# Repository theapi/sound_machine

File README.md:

# sound_machine
Use motion to select sounds

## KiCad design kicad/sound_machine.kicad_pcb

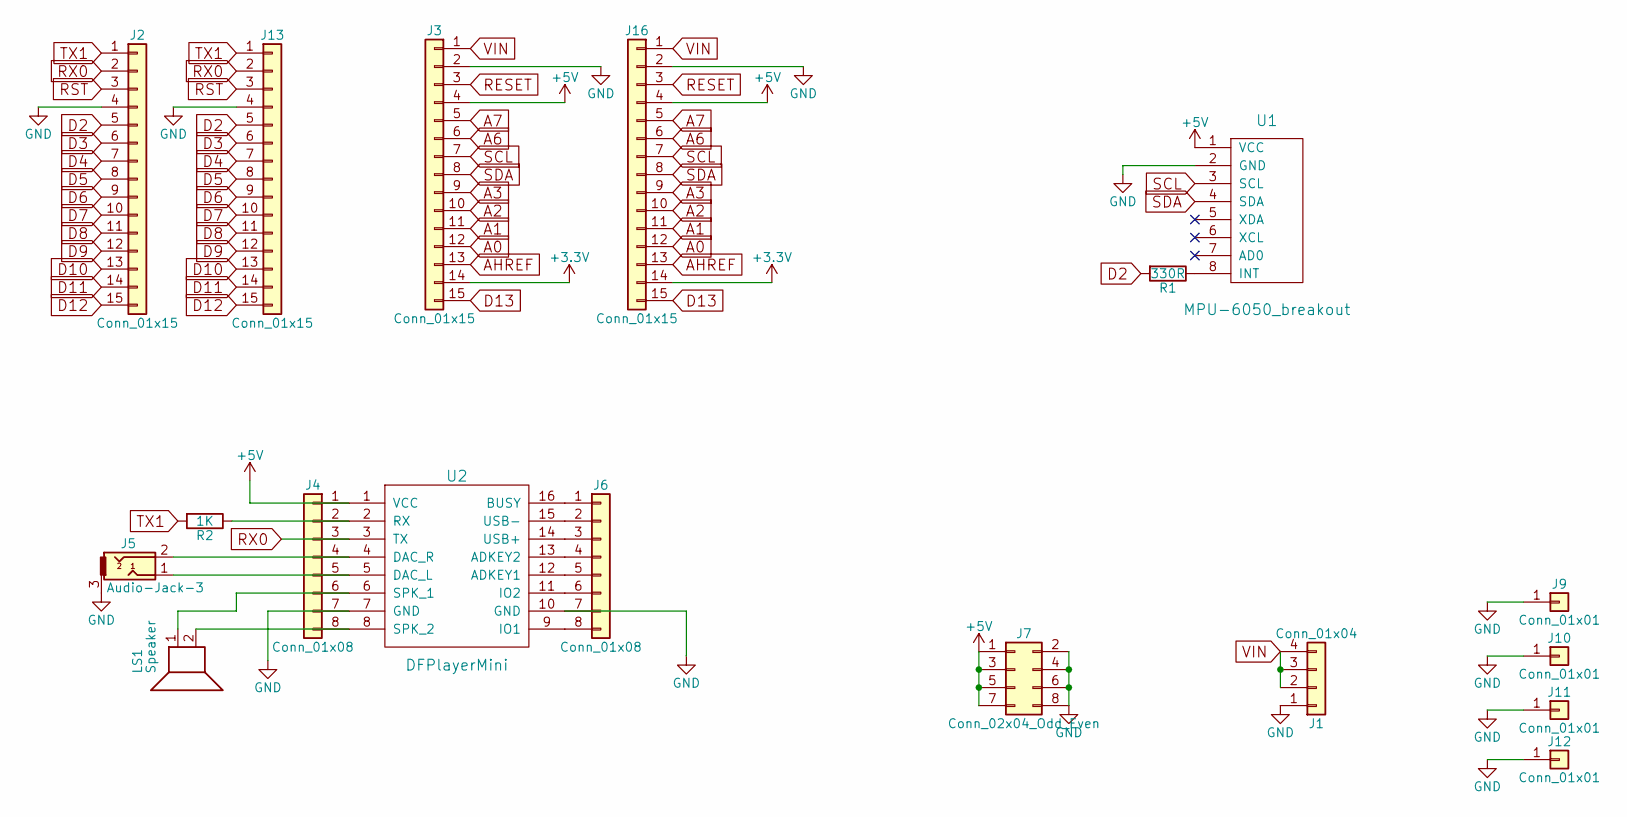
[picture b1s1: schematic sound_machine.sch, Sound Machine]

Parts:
J1: Conn_01x04; Pin_Header_Straight_1x04_Pitch2.54mm
J2, J3, J13, J16: Conn_01x15; Pin_Header_Straight_1x15_Pitch2.54mm
J4, J6: Conn_01x08; Pin_Header_Straight_1x08_Pitch2.54mm
J5: Audio-Jack-3; BARREL_JACK
J7: Conn_02x04_Odd_Even; Pin_Header_Straight_2x04_Pitch2.54mm
J9, J10, J11, J12: Conn_01x01; MountingHole_3.2mm_M3_DIN965_Pad
LS1: Speaker; Pin_Header_Straight_1x02_Pitch2.54mm
R1: 330R; R_0805_HandSoldering
R2: 1K; R_0805_HandSoldering
U1: MPU-6050_breakout; MPU-6050
U2: DFPlayerMini

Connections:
+3V3: J3.14, J16.14
+5V: J3.4, J4.1, J7.1, J7.3, J7.5, J7.7, J16.4, U1.1 (VCC), U2.1 (VCC)
A0: J3.12, J16.12
A1: J3.11, J16.11
A2: J3.10, J16.10
A3: J3.9, J16.9
A6: J3.6, J16.6
A7: J3.5, J16.5
AHREF: J3.13, J16.13
D2: J2.5, J13.5, R1.2
D3: J2.6, J13.6
D4: J2.7, J13.7
D5: J2.8, J13.8
D6: J2.9, J13.9
D7: J2.10, J13.10
D8: J2.11, J13.11
D9: J2.12, J13.12
D10: J2.13, J13.13
D11: J2.14, J13.14
D12: J2.15, J13.15
D13: J3.15, J16.15
GND: J1.1, J2.4, J3.2, J4.7, J5.3, J6.7, J7.2, J7.4, J7.6, J7.8, J9.1, J10.1, J11.1, J12.1, J13.4, J16.2, U1.2 (GND), U2.7 (GND), U2.10 (GND)
unnamed: J4.2, R2.1, U2.2 (RX)
unnamed: J4.4, J5.2, U2.4 (DAC_R)
unnamed: J4.5, J5.1, U2.5 (DAC_L)
unnamed: J4.6, LS1.1, U2.6 (SPK_1)
unnamed: J4.8, LS1.2, U2.8 (SPK_2)
unnamed: J6.1, U2.16 (BUSY)
unnamed: J6.2, U2.15 (USB-)
unnamed: J6.3, U2.14 (USB+)
unnamed: J6.4, U2.13 (ADKEY2)
unnamed: J6.5, U2.12 (ADKEY1)
unnamed: J6.6, U2.11 (IO2)
unnamed: J6.8, U2.9 (IO1)
unnamed: R1.1, U1.8 (INT)
RESET: J3.3, J16.3
RST: J2.3, J13.3
RX0: J2.2, J4.3, J13.2, U2.3 (TX)
SCL: J3.7, J16.7, U1.3 (SCL)
SDA: J3.8, J16.8, U1.4 (SDA)
TX1: J2.1, J13.1, R2.2
VIN: J1.2, J1.3, J1.4, J3.1, J16.1

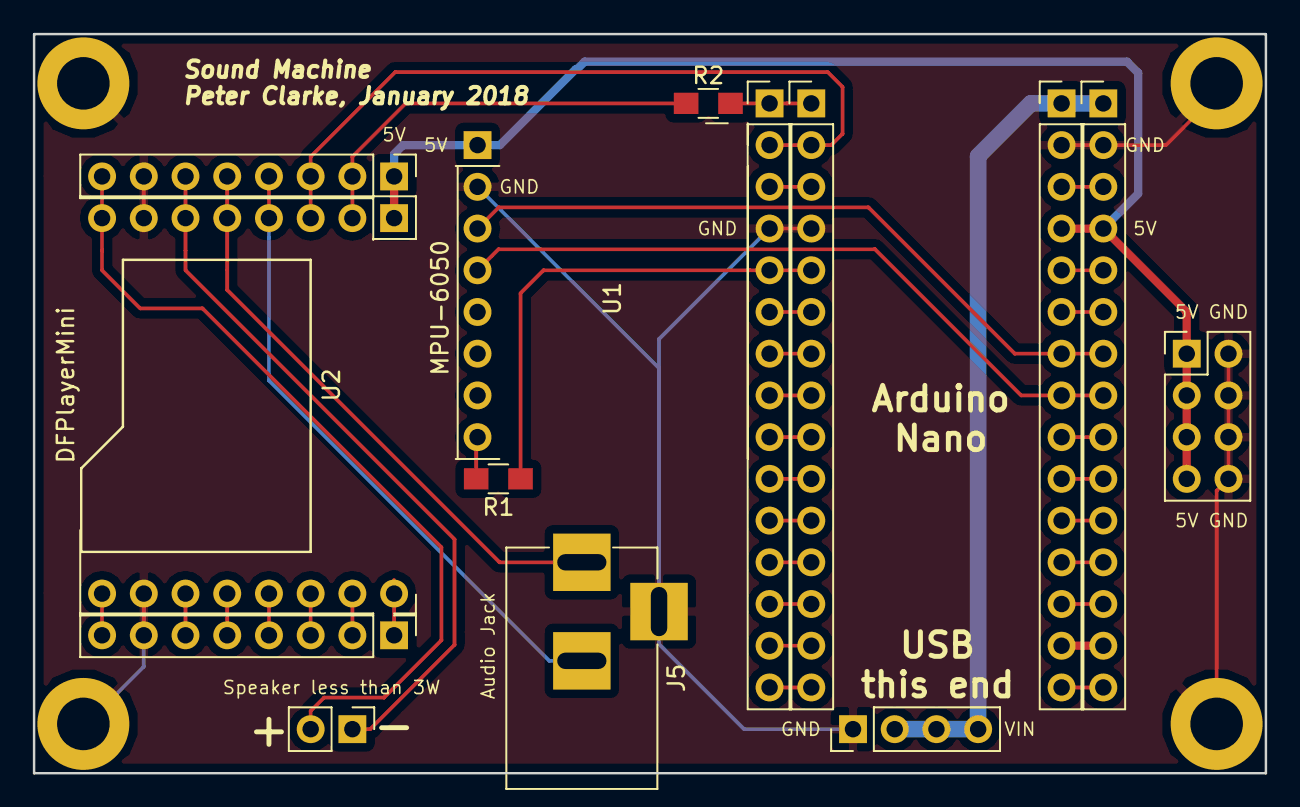
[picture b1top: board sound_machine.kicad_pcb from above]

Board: 2 copper layers, 75.0 x 45.0 mm, 18 parts (0 on the bottom side), 42 nets.

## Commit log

2017-08-24 DFPlayer datasheets
2017-08-25 MPU-6050 datasheets
2017-08-25 MPU6050 libraries
2017-08-25 DFPlayerMini library
2017-08-25 Updated .gitignore
2017-08-25 Smoke test
2017-08-25 Start of the schematic
2017-08-25 Speaker
2017-08-27 Translated doc
2017-09-02 Add a delay
2017-10-22 Basic control of the DFPlayer
2017-12-22 Nano connections
2017-12-22 Schematic done
2017-12-22 Removed redundant parts
2017-12-22 Basic layout
2017-12-22 Mounting holes
2017-12-22 Nano expansion
2017-12-23 Connected
2017-12-23 Smaller board
2017-12-23 Labels
2017-12-23 Logos & labels
2017-12-23 Gerbers
2017-12-26 Hardware as a submodule
2018-02-11 Start of motion controlled mp3 player
2018-02-11 Latest hardware
2018-02-13 Play next track when the button is pushed
2018-02-14 Print output when button pressed
